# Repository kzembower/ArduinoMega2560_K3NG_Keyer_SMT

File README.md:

# ArduinoMega2560_K3NG_Keyer_SMT

A version of the K3NG Morse Code Keyer, redrawn and built with SMD
components and pin header connections.

I intend to recreate the [K3NG Morse Code
Keyer](https://groups.io/g/radioartisan/files/K5BCQ%20-%20MEGA%202560%20MINI%20K3NG%20K5BCQ%20KEYER),
using SMT components, for automated manufacturing of the board. I also
plan to place all input and output devices, such as jacks, switches,
LCD displays, LEDs, etc. off-board, and connect to them using 0.1 inch
pitch pin headers.

I will reproduce all the current (as of 12 March 2024) functionality
of the keyer. In addition, I'd like to allow use of a USB-based
keyboard (in addition to the PS/2 style, which is increasingly hard to
find).

I will also connect all unused pins of the Arduino Mega2560 clone to
strips of 2-3 0.1 inch pads, to allow future enhancements and
experimentation.

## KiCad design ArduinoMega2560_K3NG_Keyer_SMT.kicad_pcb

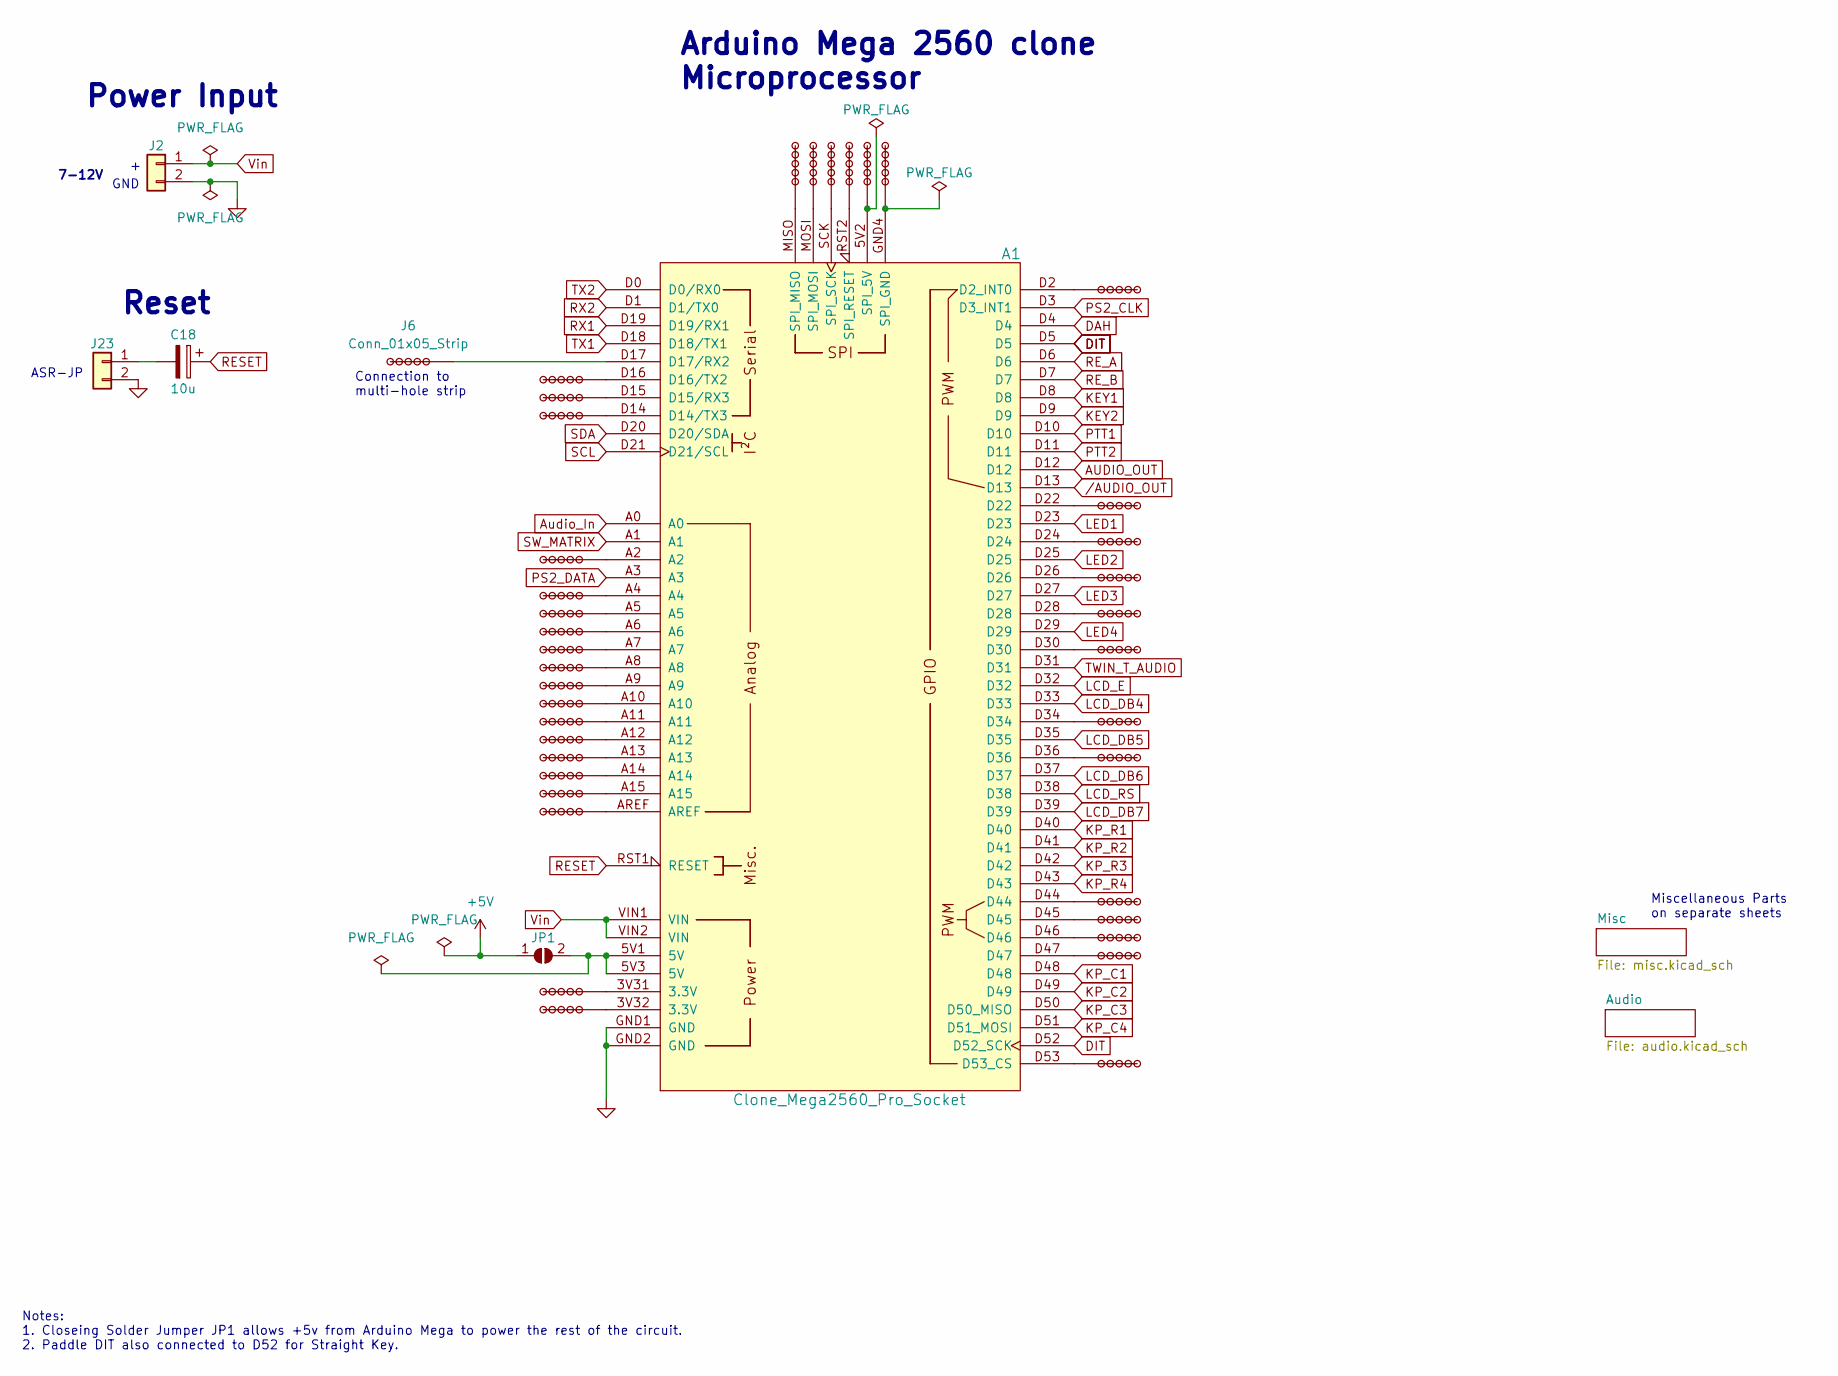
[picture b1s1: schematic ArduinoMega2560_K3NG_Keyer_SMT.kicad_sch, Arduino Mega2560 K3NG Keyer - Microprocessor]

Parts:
A1: Clone_Mega2560_Pro_Socket; JLCPCB_PN DNP
C18: 10u; CP_EIA-1608-08_AVX-J; JLCPCB_PN C1952781
J2, J23: Conn_01x02; PinHeader_1x02_P2.54mm_Vertical; JLCPCB_PN DNP
J6, J7, J8, J9, J10, J11, J12, J13, J15, J25, J26, J27, J28, J29, J30, J31, J32, J33, J34, J35, J36, J37, J38, J39, J40, J41, J42, J43, J44, J45, J46, J47, J48, J49, J50, J51, J52, J53, J54: Conn_01x05_Strip; 01x05_Strip; JLCPCB_PN DNP
JP1: SolderJumper_2_Open; SolderJumper-2_P1.3mm_Open_TrianglePad1.0x1.5mm; JLCPCB_PN DNP

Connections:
+5V: JP1.1 (A); also elsewhere on the board
AUDIO_OUT: A1.D12; also elsewhere on the board
Audio_In: A1.A0; also elsewhere on the board
DAH: A1.D4; also elsewhere on the board
DIT: A1.D5, A1.D52 (D52_SCK); also elsewhere on the board
GND: A1.GND1 (GND), A1.GND2 (GND), J2.2, J23.2; also elsewhere on the board
KEY1: A1.D8; also elsewhere on the board
KEY2: A1.D9; also elsewhere on the board
KP_C1: A1.D48; also elsewhere on the board
KP_C2: A1.D49; also elsewhere on the board
KP_C3: A1.D50 (D50_MISO); also elsewhere on the board
KP_C4: A1.D51 (D51_MOSI); also elsewhere on the board
KP_R1: A1.D40; also elsewhere on the board
KP_R2: A1.D41; also elsewhere on the board
KP_R3: A1.D42; also elsewhere on the board
KP_R4: A1.D43; also elsewhere on the board
LCD_DB4: A1.D33; also elsewhere on the board
LCD_DB5: A1.D35; also elsewhere on the board
LCD_DB6: A1.D37; also elsewhere on the board
LCD_DB7: A1.D39; also elsewhere on the board
LCD_E: A1.D32; also elsewhere on the board
LCD_RS: A1.D38; also elsewhere on the board
LED1: A1.D23; also elsewhere on the board
LED2: A1.D25; also elsewhere on the board
LED3: A1.D27; also elsewhere on the board
LED4: A1.D29; also elsewhere on the board
unnamed: A1.D2 (D2_INT0), J48.1
unnamed: A1.D14 (D14/TX3), J9.1
unnamed: A1.D15 (D15/RX3), J8.1
unnamed: A1.D16 (D16/TX2), J7.1
unnamed: A1.D17 (D17/RX2), J6.1
unnamed: A1.D53 (D53_CS), J36.1
unnamed: A1.5V2 (SPI_5V), J53.1
unnamed: A1.GND4 (SPI_GND), J54.1
unnamed: A1.MISO (SPI_MISO), J49.1
unnamed: A1.MOSI (SPI_MOSI), J50.1
unnamed: A1.RST2 (SPI_RESET), J52.1
unnamed: A1.SCK (SPI_SCK), J51.1
unnamed: A1.A2, J10.1
unnamed: A1.A4, J11.1
unnamed: A1.A5, J12.1
unnamed: A1.A6, J13.1
unnamed: A1.A7, J15.1
unnamed: C18.2, J23.1
unnamed: A1.A8, J25.1
unnamed: A1.A10, J26.1
unnamed: A1.A9, J27.1
unnamed: A1.A11, J28.1
unnamed: A1.A12, J29.1
unnamed: A1.A13, J30.1
unnamed: A1.A14, J31.1
unnamed: A1.A15, J32.1
unnamed: A1.AREF, J33.1
unnamed: A1.3V31 (3.3V), J34.1
unnamed: A1.3V32 (3.3V), J35.1
unnamed: A1.D47, J37.1
unnamed: A1.D46, J38.1
unnamed: A1.D45, J39.1
unnamed: A1.D44, J40.1
unnamed: A1.D36, J41.1
unnamed: A1.D34, J42.1
unnamed: A1.D30, J43.1
unnamed: A1.D28, J44.1
unnamed: A1.D26, J45.1
unnamed: A1.D24, J46.1
unnamed: A1.D22, J47.1
unnamed: A1.5V1 (5V), A1.5V3 (5V), JP1.2 (B)
PS2_CLK: A1.D3 (D3_INT1); also elsewhere on the board
PS2_DATA: A1.A3; also elsewhere on the board
PTT1: A1.D10; also elsewhere on the board
PTT2: A1.D11; also elsewhere on the board
RESET: A1.RST1 (RESET), C18.1
RE_A: A1.D6; also elsewhere on the board
RE_B: A1.D7; also elsewhere on the board
RX1: A1.D19 (D19/RX1); also elsewhere on the board
RX2: A1.D1 (D1/TX0); also elsewhere on the board
SCL: A1.D21 (D21/SCL); also elsewhere on the board
SDA: A1.D20 (D20/SDA); also elsewhere on the board
SW_MATRIX: A1.A1; also elsewhere on the board
TWIN_T_AUDIO: A1.D31; also elsewhere on the board
TX1: A1.D18 (D18/TX1); also elsewhere on the board
TX2: A1.D0 (D0/RX0); also elsewhere on the board
Vin: A1.VIN1 (VIN), A1.VIN2 (VIN), J2.1
/AUDIO_OUT: A1.D13

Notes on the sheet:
Arduino Mega 2560 clone Microprocessor
Reset
ASR-JP
7-12V
Notes: 1. Closeing Solder Jumper JP1 allows +5v from Arduino Mega to power the rest of the circuit. 2. Paddle DIT also connected to D52 for Straight Key.
GND
Miscellaneous Parts on separate sheets
Power Input
Connection to multi-hole strip

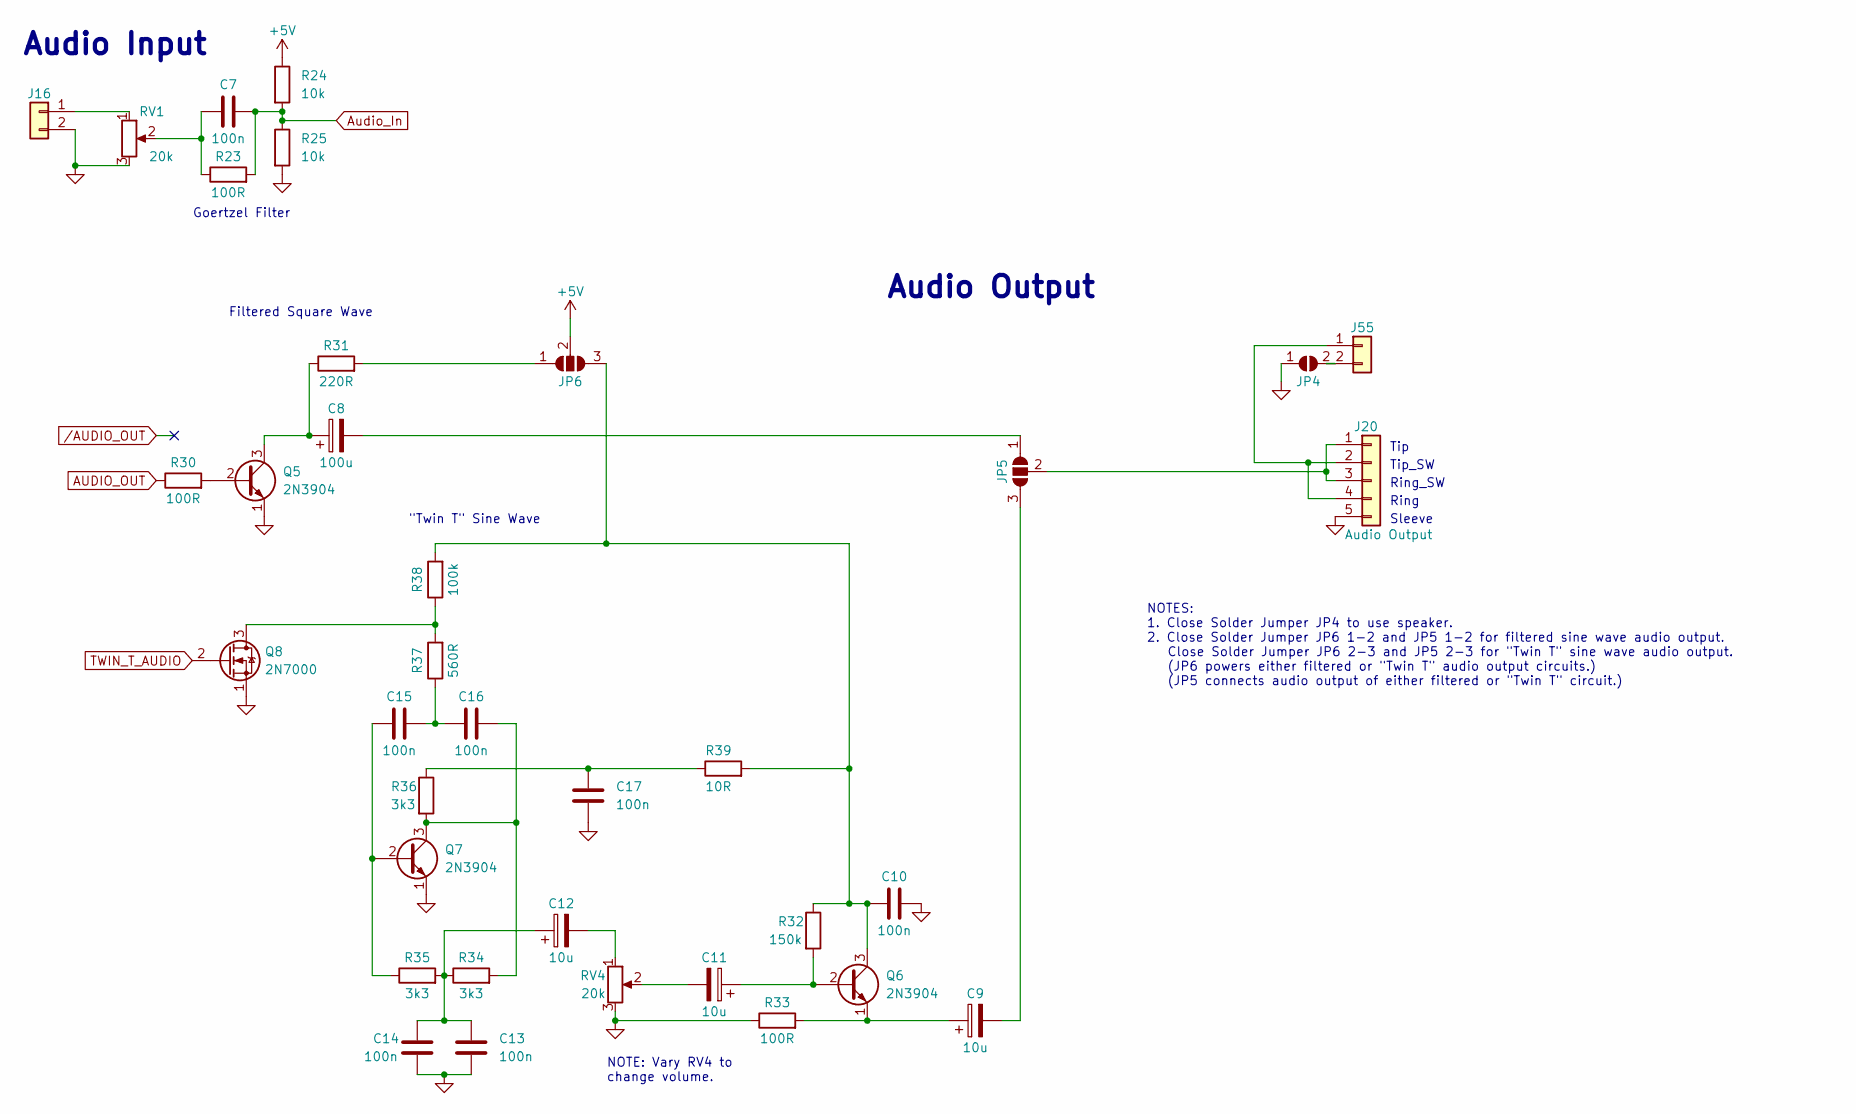
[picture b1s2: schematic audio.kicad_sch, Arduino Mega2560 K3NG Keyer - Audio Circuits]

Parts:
C7, C10, C13, C14, C15, C16, C17: 100n; C_0603_1608Metric; JLCPCB_PN C14663
C8: 100u; C_Elec_6.3x5.8; JLCPCB_PN C2972715
C9, C11, C12: 10u; CP_EIA-1608-08_AVX-J; JLCPCB_PN C1952781
J16, J55: Conn_01x02; PinHeader_1x02_P2.54mm_Vertical; JLCPCB_PN DNP
J20: Audio Output; PinHeader_1x05_P2.54mm_Vertical; JLCPCB_PN DNP
JP4: SolderJumper_2_Open; SolderJumper-2_P1.3mm_Open_TrianglePad1.0x1.5mm; JLCPCB_PN DNP
JP5, JP6: SolderJumper_3_Open; SolderJumper-3_P2.0mm_Open_TrianglePad1.0x1.5mm_NumberLabels; JLCPCB_PN DNP
Q5, Q6, Q7: 2N3904; SOT-23; JLCPCB_PN C18536
Q8: 2N7000; SOT-23; JLCPCB_PN C414015
R23, R30, R33: 100R; R_0805_2012Metric; JLCPCB_PN C17408
R24, R25: 10k; R_0805_2012Metric; JLCPCB_PN C17414
R31: 220R; R_0805_2012Metric; JLCPCB_PN C441976
R32: 150k; R_0805_2012Metric; JLCPCB_PN C543493
R34, R35, R36: 3k3; R_0805_2012Metric; JLCPCB_PN C702834
R37: 560R; R_0805_2012Metric; JLCPCB_PN C441979
R38: 100k; R_0805_2012Metric; JLCPCB_PN C441992
R39: 10R; R_0805_2012Metric; JLCPCB_PN C17415
RV1, RV4: 20k; Potentiometer_Bourns_3314J_Vertical; JLCPCB_PN C124621

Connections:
+5V: JP6.2 (C), R24.1; also elsewhere on the board
AUDIO_OUT: R30.1; also elsewhere on the board
Audio_In: C7.2, R23.2, R24.2, R25.1; also elsewhere on the board
GND: C10.2, C13.2, C14.2, C17.2, J16.2, J20.5, JP4.1 (A), Q5.1 (E), Q7.1 (E), Q8.1 (S), R25.2, R33.1, RV1.3, RV4.3; also elsewhere on the board
unnamed: C7.1, R23.1, RV1.2
unnamed: C11.2, RV4.2
unnamed: C12.1, C13.1, C14.1, R34.1, R35.2
unnamed: C12.2, RV4.1
unnamed: C15.2, C16.1, R37.1
unnamed: C17.1, R36.1, R39.1
unnamed: J16.1, RV1.1
unnamed: J20.1, J20.3, JP5.2 (C)
unnamed: J20.2, J20.4, J55.1
unnamed: J55.2, JP4.2 (B)
unnamed: C8.2, JP5.1 (A)
unnamed: C9.2, JP5.3 (B)
unnamed: JP6.1 (A), R31.2
unnamed: C10.1, JP6.3 (B), Q6.3 (C), R32.1, R38.2, R39.2
unnamed: Q5.2 (B), R30.2
unnamed: C8.1, Q5.3 (C), R31.1
unnamed: C11.1, Q6.2 (B), R32.2
unnamed: C9.1, Q6.1 (E), R33.2
unnamed: C15.1, Q7.2 (B), R35.1
unnamed: C16.2, Q7.3 (C), R34.2, R36.2
unnamed: Q8.3 (D), R37.2, R38.1
TWIN_T_AUDIO: Q8.2 (G); also elsewhere on the board

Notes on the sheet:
Filtered Square Wave
Tip
NOTE: Vary RV4 to change volume.
"Twin T" Sine Wave
Audio Input
Goertzel Filter
Ring
Sleeve
Tip_SW
NOTES: 1. Close Solder Jumper JP4 to use speaker. 2. Close Solder Jumper JP6 1-2 and JP5 1-2 for filtered sine wave audio output. Close Solder Jumper JP6 2-3 and JP5 2-3 for "Twin T" sine wave audio output. (JP6 powers either filtered or "Twin T" audio output circuits.) (JP5 connects audio output o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
Ring_SW
Audio Output

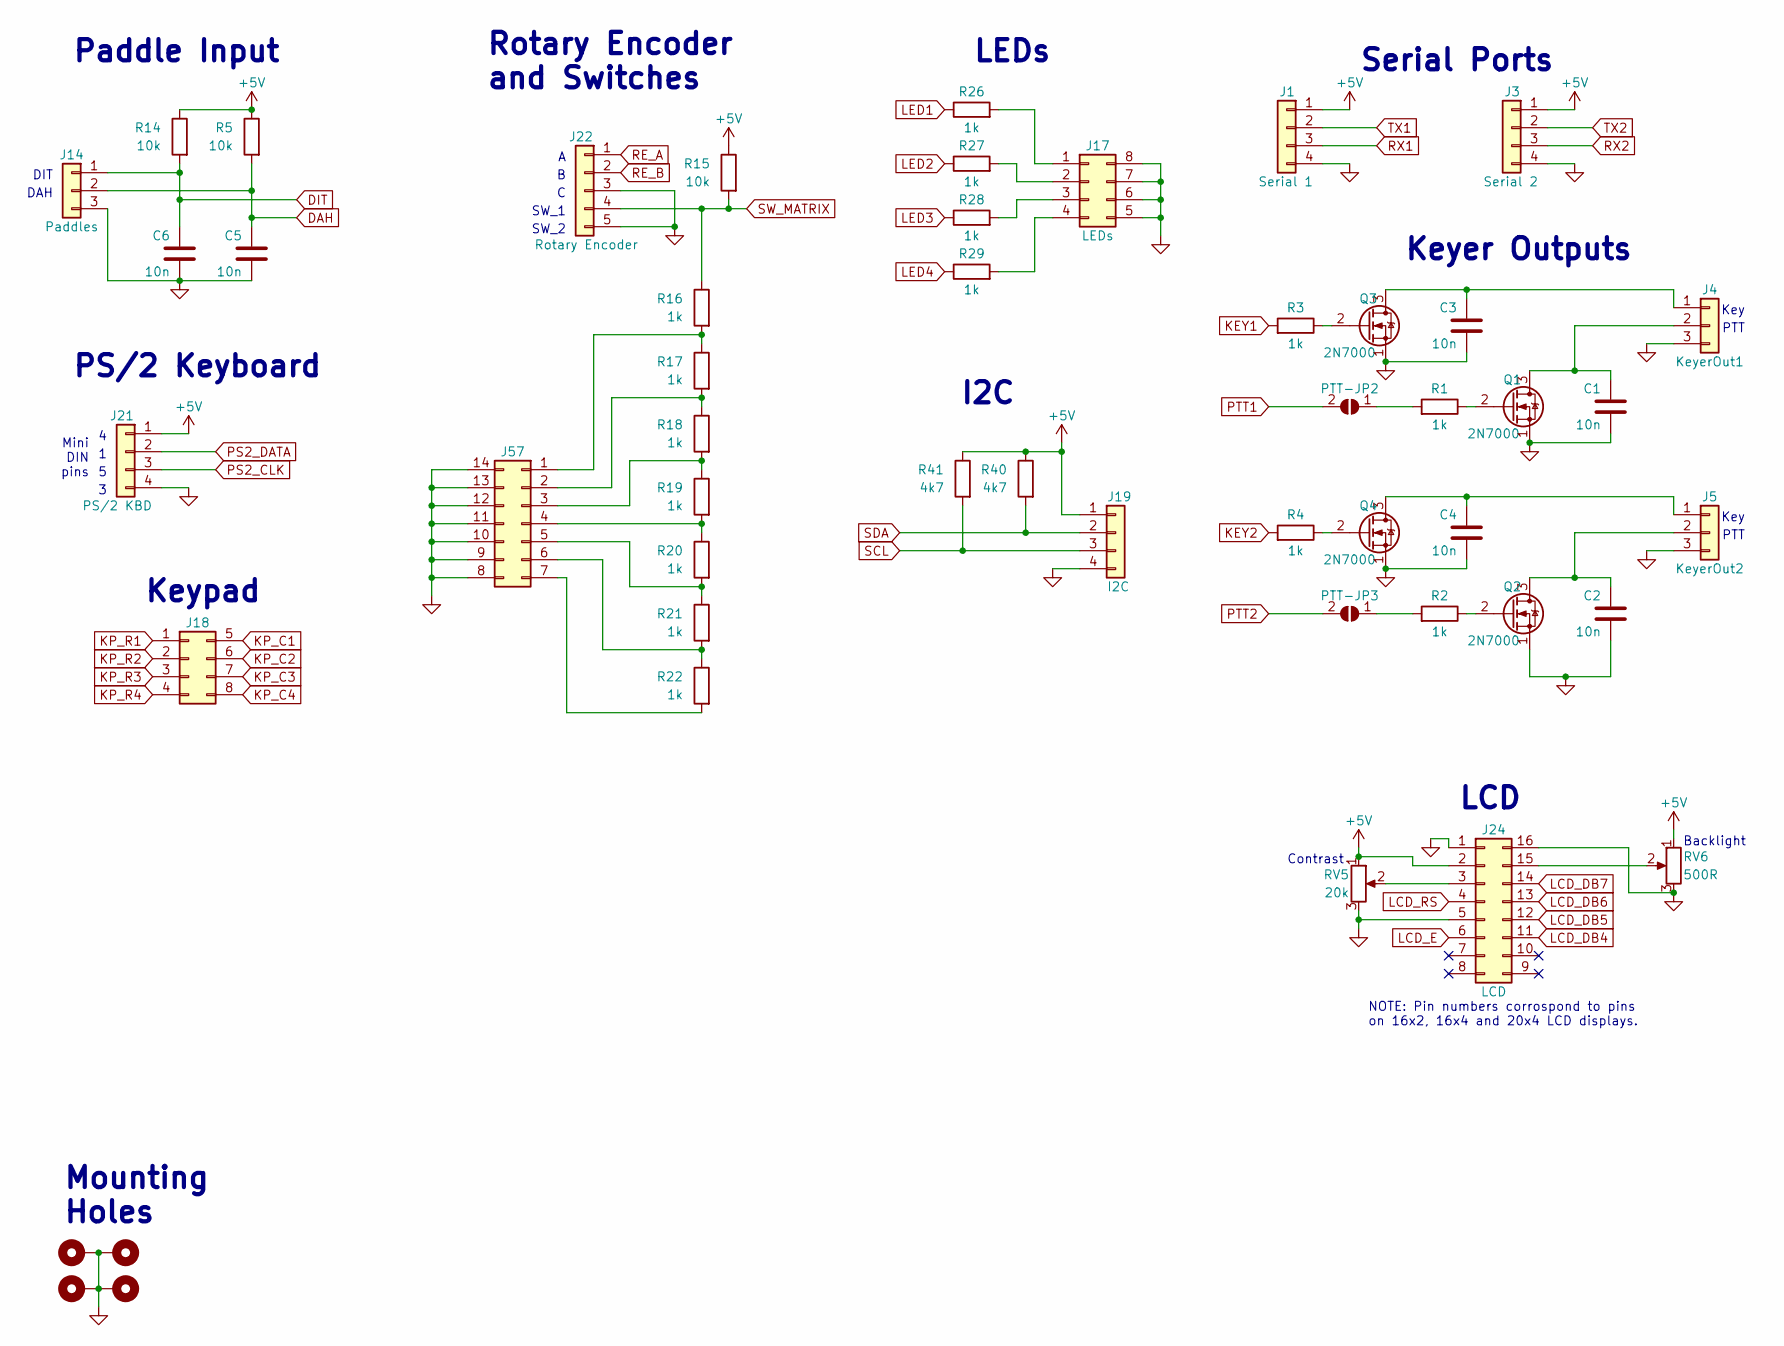
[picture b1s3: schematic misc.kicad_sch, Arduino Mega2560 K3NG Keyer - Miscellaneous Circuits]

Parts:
C1, C2, C3, C4, C5, C6: 10n; C_0603_1608Metric; JLCPCB_PN C57112
H1, H2, H3, H4: MountingHole_Pad; MountingHole_4.3mm_M4_Pad
J1: Serial 1; PinHeader_1x04_P2.54mm_Vertical; JLCPCB_PN DNP
J3: Serial 2; PinHeader_1x04_P2.54mm_Vertical; JLCPCB_PN DNP
J4: KeyerOut1; PinHeader_1x03_P2.54mm_Vertical; JLCPCB_PN DNP
J5: KeyerOut2; PinHeader_1x03_P2.54mm_Vertical; JLCPCB_PN DNP
J14: Paddles; PinHeader_1x03_P2.54mm_Vertical; JLCPCB_PN DNP
J17: LEDs; PinHeader_2x04_P2.54mm_Vertical
J18: Conn_02x04_Top_Bottom; PinHeader_2x04_P2.54mm_Vertical; JLCPCB_PN DNP
J19: I2C; PinHeader_1x04_P2.54mm_Vertical; JLCPCB_PN DNP
J21: PS/2 KBD; PinHeader_1x04_P2.54mm_Vertical; JLCPCB_PN DNP
J22: Rotary Encoder; PinHeader_1x05_P2.54mm_Vertical; JLCPCB_PN DNP
J24: LCD; PinHeader_2x08_P2.54mm_Vertical; JLCPCB_PN DNP
J57: Conn_02x07_Counter_Clockwise; PinHeader_2x07_P2.54mm_Vertical
PTT-JP2, PTT-JP3: SolderJumper_2_Open; SolderJumper-2_P1.3mm_Open_TrianglePad1.0x1.5mm; JLCPCB_PN DNP
Q1, Q2, Q3, Q4: 2N7000; SOT-23; JLCPCB_PN C414015
R1, R2, R3, R4, R16, R17, R18, R19, R20, R21, R22, R26, R27, R28, R29: 1k; R_0805_2012Metric; JLCPCB_PN C4033501
R5, R14, R15: 10k; R_0805_2012Metric; JLCPCB_PN C17414
R40, R41: 4k7; R_0805_2012Metric; JLCPCB_PN C17673
RV5: 20k; Potentiometer_Bourns_3314J_Vertical; JLCPCB_PN C124621
RV6: 500R; Potentiometer_Bourns_3314J_Vertical; JLCPCB_PN C123873

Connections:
+5V: J1.1, J3.1, J19.1, J21.1, J24.2, R5.1, R14.1, R15.1, R40.1, R41.1, RV5.1, RV6.1; also elsewhere on the board
DAH: C5.1, J14.2, R5.2; also elsewhere on the board
DIT: C6.1, J14.1, R14.2; also elsewhere on the board
GND: C1.2, C2.2, C3.2, C4.2, C5.2, C6.2, H1.1, H2.1, H3.1, H4.1, J1.4, J3.4, J4.3, J5.3, J14.3, J17.5, J17.6, J17.7, J17.8, J19.4, J21.4, J22.3, J22.5, J24.1, J24.5, J24.16, J57.8, J57.9, J57.10, J57.11, J57.12, J57.13, J57.14, Q1.1 (S), Q2.1 (S), Q3.1 (S), Q4.1 (S), RV5.3, RV6.3; also elsewhere on the board
KEY1: R3.2; also elsewhere on the board
KEY2: R4.2; also elsewhere on the board
KP_C1: J18.5; also elsewhere on the board
KP_C2: J18.6; also elsewhere on the board
KP_C3: J18.7; also elsewhere on the board
KP_C4: J18.8; also elsewhere on the board
KP_R1: J18.1; also elsewhere on the board
KP_R2: J18.2; also elsewhere on the board
KP_R3: J18.3; also elsewhere on the board
KP_R4: J18.4; also elsewhere on the board
LCD_DB4: J24.11; also elsewhere on the board
LCD_DB5: J24.12; also elsewhere on the board
LCD_DB6: J24.13; also elsewhere on the board
LCD_DB7: J24.14; also elsewhere on the board
LCD_E: J24.6; also elsewhere on the board
LCD_RS: J24.4; also elsewhere on the board
LED1: R26.1; also elsewhere on the board
LED2: R27.1; also elsewhere on the board
LED3: R28.1; also elsewhere on the board
LED4: R29.1; also elsewhere on the board
unnamed: C3.1, J4.1, Q3.3 (D)
unnamed: C1.1, J4.2, Q1.3 (D)
unnamed: C4.1, J5.1, Q4.3 (D)
unnamed: C2.1, J5.2, Q2.3 (D)
unnamed: J17.1, R26.2
unnamed: J17.2, R27.2
unnamed: J17.3, R28.2
unnamed: J17.4, R29.2
unnamed: J24.3, RV5.2
unnamed: J24.15, RV6.2
unnamed: J57.1, R16.2, R17.1
unnamed: J57.2, R17.2, R18.1
unnamed: J57.3, R18.2, R19.1
unnamed: J57.4, R19.2, R20.1
unnamed: J57.5, R20.2, R21.1
unnamed: J57.6, R21.2, R22.1
unnamed: J57.7, R22.2
unnamed: PTT-JP2.1 (A), R1.2
unnamed: PTT-JP3.1 (A), R2.2
unnamed: Q1.2 (G), R1.1
unnamed: Q2.2 (G), R2.1
unnamed: Q3.2 (G), R3.1
unnamed: Q4.2 (G), R4.1
PS2_CLK: J21.3; also elsewhere on the board
PS2_DATA: J21.2; also elsewhere on the board
PTT1: PTT-JP2.2 (B); also elsewhere on the board
PTT2: PTT-JP3.2 (B); also elsewhere on the board
RE_A: J22.1; also elsewhere on the board
RE_B: J22.2; also elsewhere on the board
RX1: J1.3; also elsewhere on the board
RX2: J3.3; also elsewhere on the board
SCL: J19.3, R41.2; also elsewhere on the board
SDA: J19.2, R40.2; also elsewhere on the board
SW_MATRIX: J22.4, R15.2, R16.1; also elsewhere on the board
TX1: J1.2; also elsewhere on the board
TX2: J3.2; also elsewhere on the board

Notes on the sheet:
SW_1
LCD
DIT
Paddle Input
Mini DIN pins
PTT
DAH
Key
Mounting Holes
Backlight
Keyer Outputs
I2C
PS/2 Keyboard
Keypad
Serial Ports
SW_2
Rotary Encoder and Switches
Contrast
NOTE: Pin numbers corrospond to pins on 16x2, 16x4 and 20x4 LCD displays.
LEDs

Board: 2 copper layers, 130 parts (0 on the bottom side), 127 nets, no tracks yet.

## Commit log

2024-03-12 Initial commitment of first draft of all documents.
2024-03-12 Renamed untitled.kicad_sch to misc.kicad_sch (Sheet for miscellaeous parts of circuit).
2024-03-12 Small drawing cleanups.
2024-03-12 Added .pdf for the schematic drawings.
2024-03-12 Elaborate in the README.md.
2024-03-12 Changed power jack and LCD symbols.
2024-03-12 Cosmetic changes.
2024-03-12 Removed version of Rotary Encoder and Switches that didn't use 2x8 pin connector.
2024-03-14 Minor changes. Added mounting holes.
2024-03-16 Added multi-hole strips to unused pins on Arduino Mega 2560 microprocessor. Also, some minor changes.
2024-03-16 Forgot to update .pdf files. Also modified .gitignore to ignore fp-info-cache file.
2024-03-18 Updated .pdf.
2024-03-18 First attempt at assigning footprints and JLCPCB part numbers.
2024-03-18 Added PWR_FLAG and others to correct ERC errors. All ERC errors corrected; no errors or warnings present.
2024-03-19 Unknown (minor) changes.
2024-03-19 Changed many capacitor part numbers.
2024-03-19 Fixed variable resistor parts.
2024-03-19 Fixed variable resistor parts (forgot to save before committing).
2024-03-23 First attempt at locating parts on PCB. Also, many changes to footprints.
2024-03-23 Added _autosave* files to .gitignore.
